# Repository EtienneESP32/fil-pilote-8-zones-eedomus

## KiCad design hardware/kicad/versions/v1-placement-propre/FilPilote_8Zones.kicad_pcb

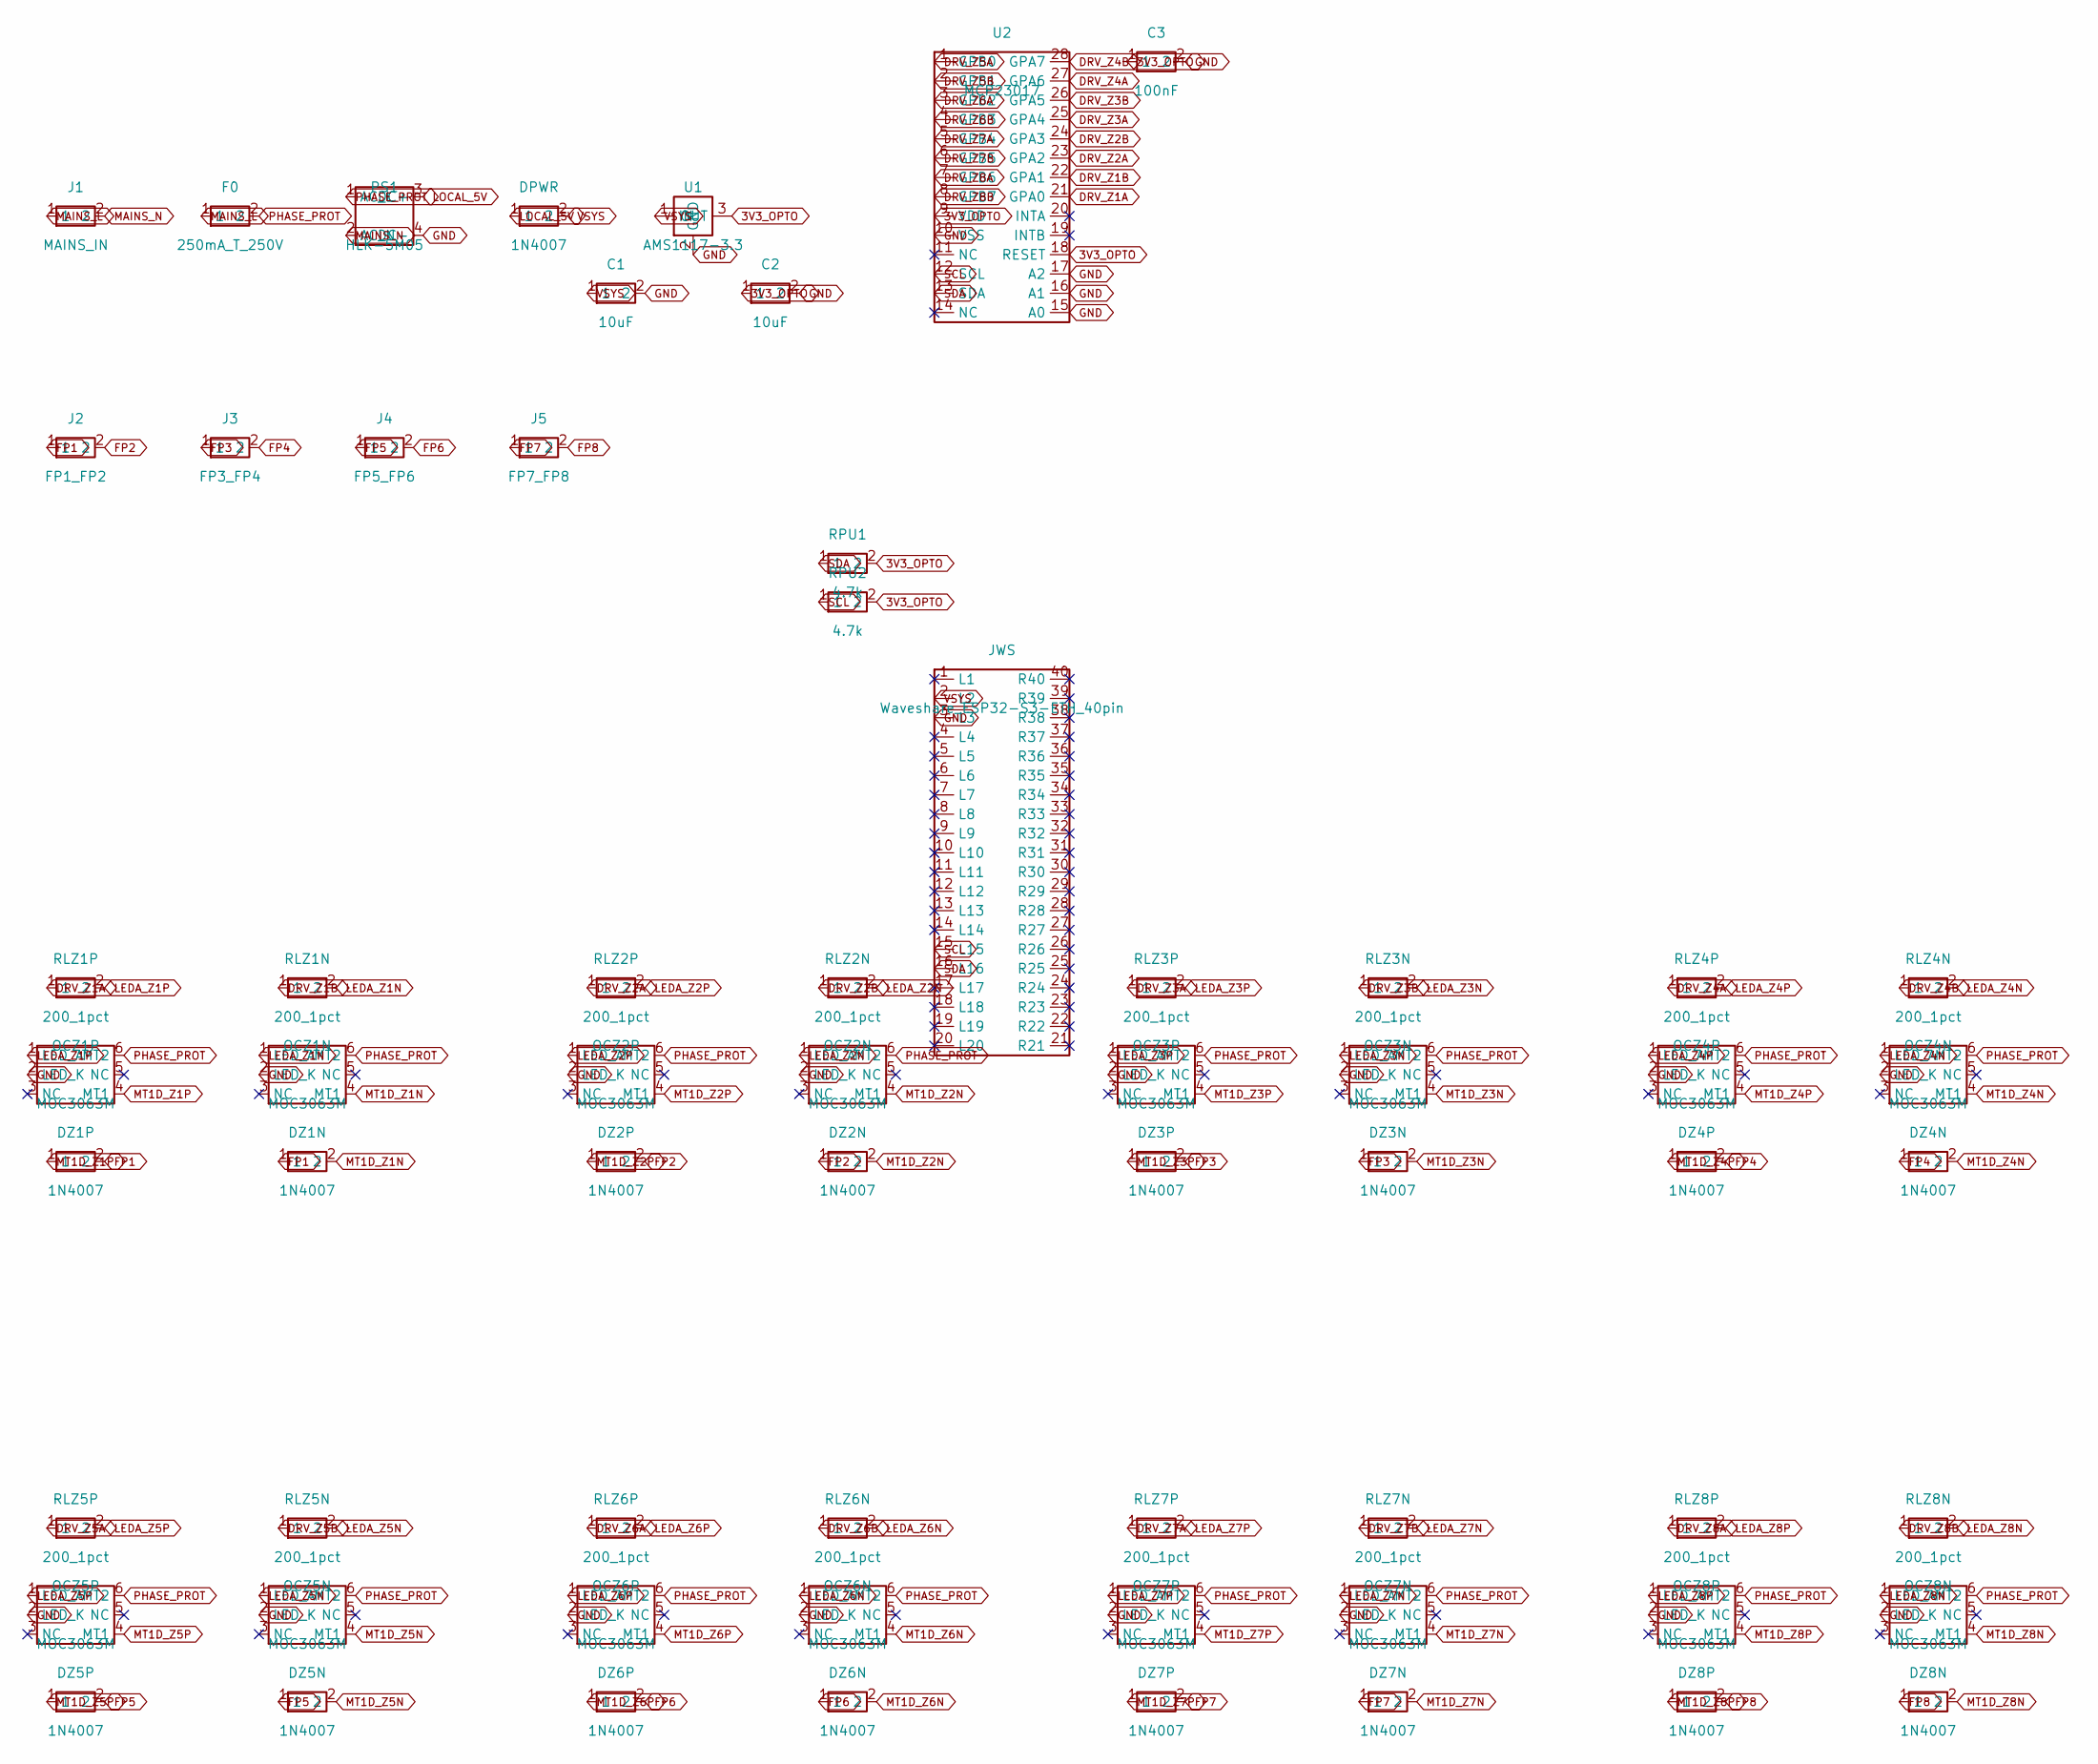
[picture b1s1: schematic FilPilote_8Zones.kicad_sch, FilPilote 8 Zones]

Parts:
C1, C2: 10uF; Radial_THT
C3: 100nF; Radial_THT
DPWR: 1N4007; DO41_THT
DZ1N, DZ1P, DZ2N, DZ2P, DZ3N, DZ3P, DZ4N, DZ4P, DZ5N, DZ5P, DZ6N, DZ6P, DZ7N, DZ7P, DZ8N, DZ8P: 1N4007; DO41_THT
F0: 250mA_T_250V; Axial_THT
J1: MAINS_IN; TerminalBlock_2.54_2pin
J2: FP1_FP2; TerminalBlock_5.08_2pin
J3: FP3_FP4; TerminalBlock_5.08_2pin
J4: FP5_FP6; TerminalBlock_5.08_2pin
J5: FP7_FP8; TerminalBlock_5.08_2pin
JWS: Waveshare_ESP32-S3-ETH_40pin; PinHeader_2x20_2.54_Pico
OCZ1N, OCZ1P, OCZ2N, OCZ2P, OCZ3N, OCZ3P, OCZ4N, OCZ4P, OCZ5N, OCZ5P, OCZ6N, OCZ6P, OCZ7N, OCZ7P, OCZ8N, OCZ8P: MOC3063M; DIP6_THT
PS1: HLK-5M05; Module_PSU4
RLZ1N, RLZ1P, RLZ2N, RLZ2P, RLZ3N, RLZ3P, RLZ4N, RLZ4P, RLZ5N, RLZ5P, RLZ6N, RLZ6P, RLZ7N, RLZ7P, RLZ8N, RLZ8P: 200_1pct; Axial_THT
RPU1, RPU2: 4.7k; Axial_THT
U1: AMS1117-3.3; TO220_THT
U2: MCP23017; DIP28_THT

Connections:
3V3_OPTO: C2.1, C3.1, RPU1.2, RPU2.2, U1.3 (OUT), U2.9 (VDD), U2.18 (RESET)
DRV_Z1A: RLZ1P.1, U2.21 (GPA0)
DRV_Z1B: RLZ1N.1, U2.22 (GPA1)
DRV_Z2A: RLZ2P.1, U2.23 (GPA2)
DRV_Z2B: RLZ2N.1, U2.24 (GPA3)
DRV_Z3A: RLZ3P.1, U2.25 (GPA4)
DRV_Z3B: RLZ3N.1, U2.26 (GPA5)
DRV_Z4A: RLZ4P.1, U2.27 (GPA6)
DRV_Z4B: RLZ4N.1, U2.28 (GPA7)
DRV_Z5A: RLZ5P.1, U2.1 (GPB0)
DRV_Z5B: RLZ5N.1, U2.2 (GPB1)
DRV_Z6A: RLZ6P.1, U2.3 (GPB2)
DRV_Z6B: RLZ6N.1, U2.4 (GPB3)
DRV_Z7A: RLZ7P.1, U2.5 (GPB4)
DRV_Z7B: RLZ7N.1, U2.6 (GPB5)
DRV_Z8A: RLZ8P.1, U2.7 (GPB6)
DRV_Z8B: RLZ8N.1, U2.8 (GPB7)
FP1: DZ1N.1, DZ1P.2, J2.1
FP2: DZ2N.1, DZ2P.2, J2.2
FP3: DZ3N.1, DZ3P.2, J3.1
FP4: DZ4N.1, DZ4P.2, J3.2
FP5: DZ5N.1, DZ5P.2, J4.1
FP6: DZ6N.1, DZ6P.2, J4.2
FP7: DZ7N.1, DZ7P.2, J5.1
FP8: DZ8N.1, DZ8P.2, J5.2
GND: C1.2, C2.2, C3.2, JWS.3 (L3), OCZ1N.2 (LED_K), OCZ1P.2 (LED_K), OCZ2N.2 (LED_K), OCZ2P.2 (LED_K), OCZ3N.2 (LED_K), OCZ3P.2 (LED_K), OCZ4N.2 (LED_K), OCZ4P.2 (LED_K), OCZ5N.2 (LED_K), OCZ5P.2 (LED_K), OCZ6N.2 (LED_K), OCZ6P.2 (LED_K), OCZ7N.2 (LED_K), OCZ7P.2 (LED_K), OCZ8N.2 (LED_K), OCZ8P.2 (LED_K), PS1.4 (DC-), U1.2 (GND), U2.10 (VSS), U2.15 (A0), U2.16 (A1), U2.17 (A2)
LEDA_Z1N: OCZ1N.1 (LED_A), RLZ1N.2
LEDA_Z1P: OCZ1P.1 (LED_A), RLZ1P.2
LEDA_Z2N: OCZ2N.1 (LED_A), RLZ2N.2
LEDA_Z2P: OCZ2P.1 (LED_A), RLZ2P.2
LEDA_Z3N: OCZ3N.1 (LED_A), RLZ3N.2
LEDA_Z3P: OCZ3P.1 (LED_A), RLZ3P.2
LEDA_Z4N: OCZ4N.1 (LED_A), RLZ4N.2
LEDA_Z4P: OCZ4P.1 (LED_A), RLZ4P.2
LEDA_Z5N: OCZ5N.1 (LED_A), RLZ5N.2
LEDA_Z5P: OCZ5P.1 (LED_A), RLZ5P.2
LEDA_Z6N: OCZ6N.1 (LED_A), RLZ6N.2
LEDA_Z6P: OCZ6P.1 (LED_A), RLZ6P.2
LEDA_Z7N: OCZ7N.1 (LED_A), RLZ7N.2
LEDA_Z7P: OCZ7P.1 (LED_A), RLZ7P.2
LEDA_Z8N: OCZ8N.1 (LED_A), RLZ8N.2
LEDA_Z8P: OCZ8P.1 (LED_A), RLZ8P.2
LOCAL_5V: DPWR.1, PS1.3 (DC+)
MAINS_L: F0.1, J1.1
MAINS_N: J1.2, PS1.2 (AC_N)
MT1D_Z1N: DZ1N.2, OCZ1N.4 (MT1)
MT1D_Z1P: DZ1P.1, OCZ1P.4 (MT1)
MT1D_Z2N: DZ2N.2, OCZ2N.4 (MT1)
MT1D_Z2P: DZ2P.1, OCZ2P.4 (MT1)
MT1D_Z3N: DZ3N.2, OCZ3N.4 (MT1)
MT1D_Z3P: DZ3P.1, OCZ3P.4 (MT1)
MT1D_Z4N: DZ4N.2, OCZ4N.4 (MT1)
MT1D_Z4P: DZ4P.1, OCZ4P.4 (MT1)
MT1D_Z5N: DZ5N.2, OCZ5N.4 (MT1)
MT1D_Z5P: DZ5P.1, OCZ5P.4 (MT1)
MT1D_Z6N: DZ6N.2, OCZ6N.4 (MT1)
MT1D_Z6P: DZ6P.1, OCZ6P.4 (MT1)
MT1D_Z7N: DZ7N.2, OCZ7N.4 (MT1)
MT1D_Z7P: DZ7P.1, OCZ7P.4 (MT1)
MT1D_Z8N: DZ8N.2, OCZ8N.4 (MT1)
MT1D_Z8P: DZ8P.1, OCZ8P.4 (MT1)
PHASE_PROT: F0.2, OCZ1N.6 (MT2), OCZ1P.6 (MT2), OCZ2N.6 (MT2), OCZ2P.6 (MT2), OCZ3N.6 (MT2), OCZ3P.6 (MT2), OCZ4N.6 (MT2), OCZ4P.6 (MT2), OCZ5N.6 (MT2), OCZ5P.6 (MT2), OCZ6N.6 (MT2), OCZ6P.6 (MT2), OCZ7N.6 (MT2), OCZ7P.6 (MT2), OCZ8N.6 (MT2), OCZ8P.6 (MT2), PS1.1 (AC_L)
SCL: JWS.15 (L15), RPU2.1, U2.12 (SCL)
SDA: JWS.16 (L16), RPU1.1, U2.13 (SDA)
VSYS: C1.1, DPWR.2, JWS.2 (L2), U1.1 (IN)

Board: 2 copper layers, 64 parts (0 on the bottom side), 65 nets, no tracks yet.

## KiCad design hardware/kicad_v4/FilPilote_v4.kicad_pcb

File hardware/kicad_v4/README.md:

# Fil pilote 8 zones — carte v4

Carte KiCad 10 qui commande huit radiateurs par fil pilote depuis un ESP32-S3 en Ethernet.

> **Danger : 230 V.** Cette carte n'a encore été ni fabriquée ni essayée. Elle doit être relue par une personne qualifiée avant tout raccordement au secteur. L'ancienne carte, dans [`hardware/kicad`](../kicad), ne doit pas être fabriquée.

## Caractéristiques

- 156,0 x 86,5 mm, 2 couches, FR4 1,6 mm, pour coffret rail DIN CamdenBoss CNMB/9.
- Contrôleur Waveshare ESP32-S3-ETH-M (sans PoE), enfiché sur deux barrettes.
- Par zone : deux optotriacs MOC3063M et deux diodes 1N4007, un pour chaque alternance.
- Alimentation isolée Mean Well IRM-05-5, fusible 250 mA T à l'entrée.
- Composants traversants uniquement. Circuits intégrés, optos et ESP32 sur supports.

## Schéma

## Vues

Dessus :

Dessous :

Placement coté :

Cuivre, deux faces :

Dans le coffret (modèle simplifié, en partie relevé à l'échelle) :

## Contrôles

| Contrôle | Résultat |
|---|---|
| DRC, règle secteur / très basse tension de 6 mm active | 0 erreur, 0 avertissement |
| Connexions manquantes, écarts avec le schéma, ERC | 0 |
| Distance secteur / très basse tension, recalculée sans le DRC | 6,02 mm minimum (nominal) |
| Pastilles comparées aux fiches techniques | 309 sur 309 conformes |
| Gerbers relus sans KiCad | 6,02 mm minimum, 313 trous métallisés sur 313 |

Pas encore vérifié : distance entre les lames des supports d'optos (leur fiche annonce 1000 V RMS), essai des vraies pièces sur l'impression 1:1, position des fenêtres du coffret.

## Fichiers

| Fichier | Contenu |
|---|---|
| [`FilPilote_v4.kicad_pro`](FilPilote_v4.kicad_pro) | Projet KiCad 10 |
| [`FilPilote_v4.kicad_dru`](FilPilote_v4.kicad_dru) | Règles d'isolement |
| [`etape5_impression_1-1.pdf`](etape5_impression_1-1.pdf) | Impression à l'échelle 1:1 |
| [`fabrication/`](fabrication) | Gerbers, perçages, consignes |
| [`tools/`](tools) | Scripts de construction et de contrôle |
| [`versions/`](versions) | Sauvegarde de chaque étape |

Détails : [empreintes](../../docs/13_Empreintes-etape1.md), [routage](../../docs/14_Routage-etape4.md), [contrôle final](../../docs/15_Controle-etape5.md). Pièces : [liste RS](../../docs/Liste_RS_Particuliers.csv), [autres](../../docs/Liste_Farnell_et_autres.csv).

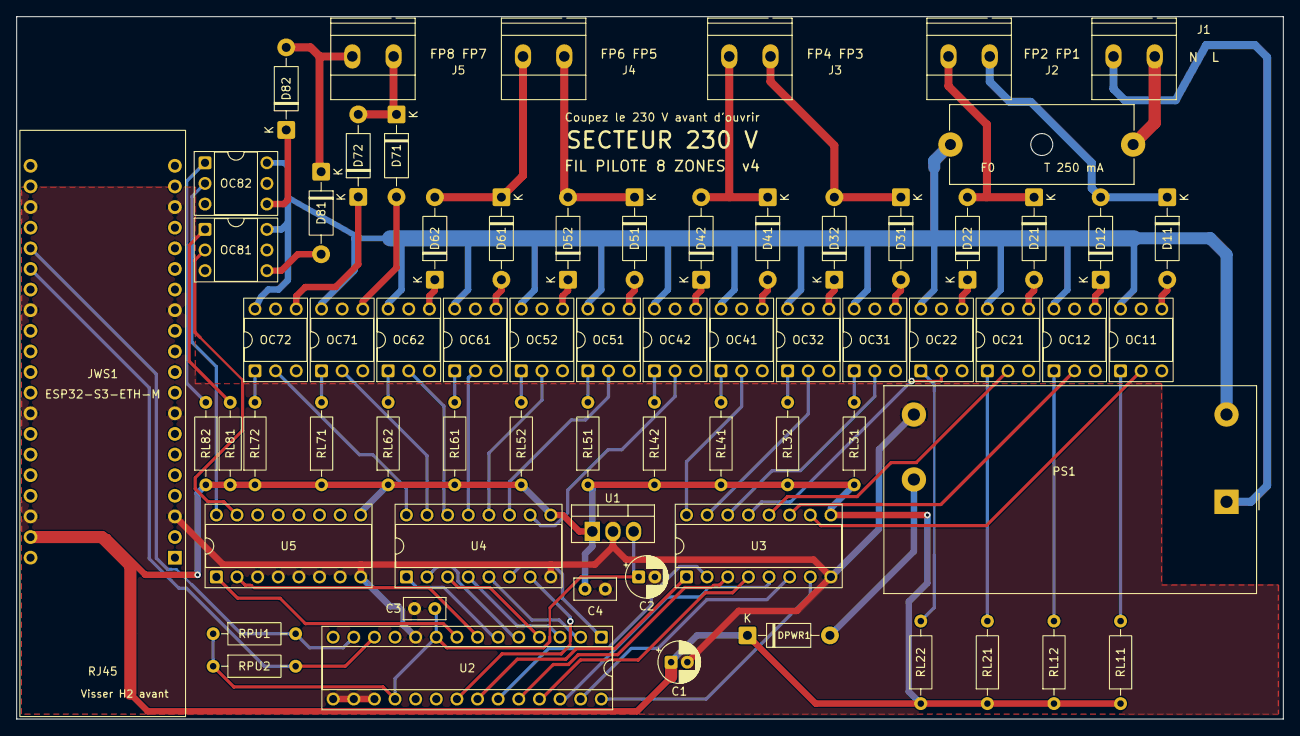
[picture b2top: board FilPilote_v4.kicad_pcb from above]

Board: 2 copper layers, 156.0 x 86.5 mm, 70 parts (0 on the bottom side), 81 nets.

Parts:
C1, C2: 47uF 25V; CP_Radial_D5.0mm_P2.00mm
C3, C4: 100nF; C_Disc_D5.0mm_W2.5mm_P2.50mm
D11, D12, D21, D22, D31, D32, D41, D42, D51, D52, D61, D62, D71, D72, D81, D82: 1N4007; D_DO-41_SOD81_P10.16mm_Horizontal
DPWR1: 1N5819RL; D_DO-41_SOD81_P10.16mm_Horizontal
F0: 250mA T 5x20; Schurter_0031.8201
H1, H2: Fixation coffret; Fixation_CNMB_4.0x10.4
J1: SECTEUR L/N; Phoenix_1715721_MKDS-1.5-2-5.08
J2: FP1 / FP2; Phoenix_1715721_MKDS-1.5-2-5.08
J3: FP3 / FP4; Phoenix_1715721_MKDS-1.5-2-5.08
J4: FP5 / FP6; Phoenix_1715721_MKDS-1.5-2-5.08
J5: FP7 / FP8; Phoenix_1715721_MKDS-1.5-2-5.08
JWS1: ESP32-S3-ETH-M; Waveshare_ESP32-S3-ETH-M
OC11, OC12, OC21, OC22, OC31, OC32, OC41, OC42, OC51, OC52, OC61, OC62, OC71, OC72, OC81, OC82: MOC3063M; DIP-6_W7.62mm_Support_ASSMANN
PS1: IRM-05-5; Converter_ACDC_MeanWell_IRM-05-xx_THT
RL11, RL12, RL21, RL22, RL31, RL32, RL41, RL42, RL51, RL52, RL61, RL62, RL71, RL72, RL81, RL82: 200 1%; R_Axial_DIN0207_L6.3mm_D2.5mm_P10.16mm_Horizontal
RPU1, RPU2: 4.7k; R_Axial_DIN0207_L6.3mm_D2.5mm_P10.16mm_Horizontal
U1: LF33CV; TO-220-3_Vertical_LF33CV
U2: MCP23017-E/SP; DIP-28_W7.62mm_Support_ASSMANN
U3, U4, U5: ULN2003AN; DIP-16_W7.62mm_Support_ASSMANN

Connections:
3V3_OPTO: C2.1, C3.1, RPU1.1, RPU2.1, U1.3, U2.9, U2.18
DRV_11: U2.28, U3.7
DRV_12: U2.27, U3.6
DRV_21: U2.26, U3.5
DRV_22: U2.25, U3.4
DRV_31: U2.24, U3.3
DRV_32: U2.23, U3.2
DRV_41: U2.22, U3.1
DRV_42: U2.21, U4.7
DRV_51: U2.1, U4.6
DRV_52: U2.2, U4.5
DRV_61: U2.3, U4.4
DRV_62: U2.4, U4.3
DRV_71: U2.5, U4.2
DRV_72: U2.6, U4.1
DRV_81: U2.7, U5.2
DRV_82: U2.8, U5.1
FP1: D11.1, D12.2, J2.1
FP2: D21.1, D22.2, J2.2
FP3: D31.1, D32.2, J3.1
FP4: D41.1, D42.2, J3.2
FP5: D51.1, D52.2, J4.1
FP6: D61.1, D62.2, J4.2
FP7: D71.1, D72.2, J5.1
FP8: D81.1, D82.2, J5.2
GND: C1.2, C2.2, C3.2, C4.2, JWS1.3, JWS1.8, JWS1.13, JWS1.18, JWS1.23, JWS1.28, JWS1.33, JWS1.38, PS1.3, U1.2, U2.10, U2.15, U2.16, U2.17, U3.8, U4.8, U5.3, U5.4, U5.5, U5.6, U5.7, U5.8
LEDA_11: OC11.1, RL11.2
LEDA_12: OC12.1, RL12.2
LEDA_21: OC21.1, RL21.2
LEDA_22: OC22.1, RL22.2
LEDA_31: OC31.1, RL31.2
LEDA_32: OC32.1, RL32.2
LEDA_41: OC41.1, RL41.2
LEDA_42: OC42.1, RL42.2
LEDA_51: OC51.1, RL51.2
LEDA_52: OC52.1, RL52.2
LEDA_61: OC61.1, RL61.2
LEDA_62: OC62.1, RL62.2
LEDA_71: OC71.1, RL71.2
LEDA_72: OC72.1, RL72.2
LEDA_81: OC81.1, RL81.2
LEDA_82: OC82.1, RL82.2
LEDK_11: OC11.2, U3.10
LEDK_12: OC12.2, U3.11
LEDK_21: OC21.2, U3.12
LEDK_22: OC22.2, U3.13
LEDK_31: OC31.2, U3.14
LEDK_32: OC32.2, U3.15
LEDK_41: OC41.2, U3.16
LEDK_42: OC42.2, U4.10
LEDK_51: OC51.2, U4.11
LEDK_52: OC52.2, U4.12
LEDK_61: OC61.2, U4.13
LEDK_62: OC62.2, U4.14
LEDK_71: OC71.2, U4.15
LEDK_72: OC72.2, U4.16
LEDK_81: OC81.2, U5.15
LEDK_82: OC82.2, U5.16
LOCAL_5V: DPWR1.2, PS1.4
MAINS_L: F0.1, J1.1
MAINS_N: J1.2, PS1.1
MT_11: D11.2, OC11.4
MT_12: D12.1, OC12.4
MT_21: D21.2, OC21.4
MT_22: D22.1, OC22.4
MT_31: D31.2, OC31.4
MT_32: D32.1, OC32.4
MT_41: D41.2, OC41.4
MT_42: D42.1, OC42.4
MT_51: D51.2, OC51.4
MT_52: D52.1, OC52.4
MT_61: D61.2, OC61.4
MT_62: D62.1, OC62.4
MT_71: D71.2, OC71.4
MT_72: D72.1, OC72.4
MT_81: D81.2, OC81.4
MT_82: D82.1, OC82.4
PHASE_PROT: F0.2, OC11.6, OC12.6, OC21.6, OC22.6, OC31.6, OC32.6, OC41.6, OC42.6, OC51.6, OC52.6, OC61.6, OC62.6, OC71.6, OC72.6, OC81.6, OC82.6, PS1.2
SCL: JWS1.26, RPU2.2, U2.12
SDA: JWS1.25, RPU1.2, U2.13
VSYS: C1.1, C4.1, DPWR1.1, JWS1.39, RL11.1, RL12.1, RL21.1, RL22.1, RL31.1, RL32.1, RL41.1, RL42.1, RL51.1, RL52.1, RL61.1, RL62.1, RL71.1, RL72.1, RL81.1, RL82.1, U1.1, U3.9, U4.9, U5.9
